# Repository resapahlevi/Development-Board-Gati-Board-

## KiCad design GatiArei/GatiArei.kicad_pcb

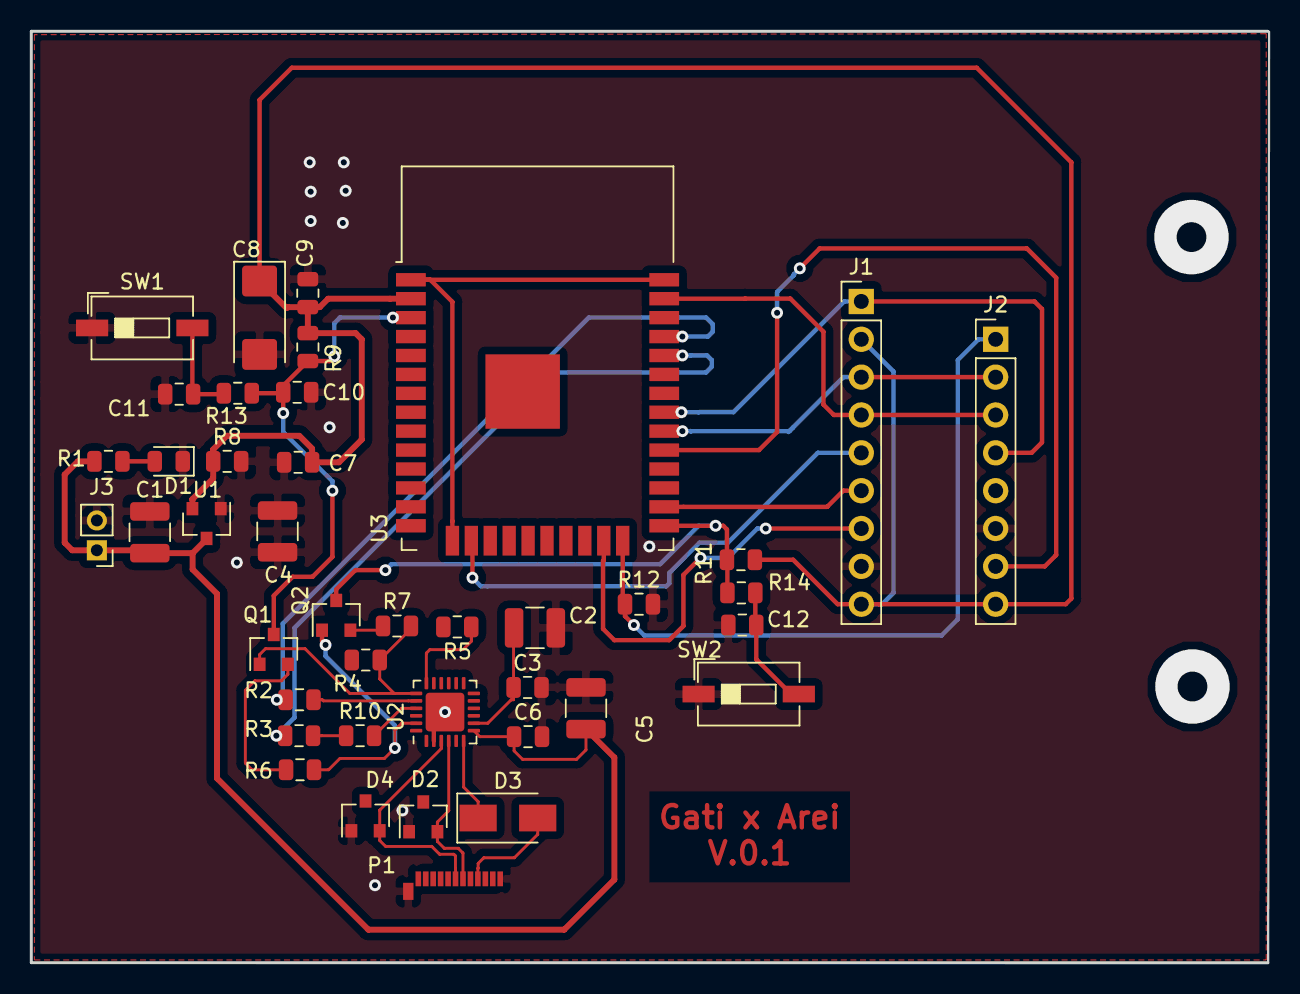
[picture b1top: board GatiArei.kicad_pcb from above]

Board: 2 copper layers, 83.1 x 62.5 mm, 41 parts (0 on the bottom side), 30 nets.

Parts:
C1, C2, C4, C5: 10uf/25v; C_1210_3225Metric
C3, C6: 0.1uf/25v; C_0805_2012Metric
C7: 22uf/25v; C_0805_2012Metric
C8: 100uf/6.3V; CP_EIA-6032-15_Kemet-U
C9: 1uf/10V; C_0805_2012Metric
C10: 1NF/50V; C_0805_2012Metric
C11, C12: 1nf/50V; C_0805_2012Metric
D1: LED_R; LED_0805_2012Metric
D2, D4: ESD5V; SOT-23
D3: 1N5819; D_SMA
J1: LCD_PORT; PinHeader_1x09_P2.54mm_Vertical
J2: RFID_PORT; PinHeader_1x08_P2.54mm_Vertical
J3: Bat_Con; PinHeader_1x02_P2.00mm_Vertical
P1: USB_C; USB_C_Plug_Molex_105444
Q1, Q2: S8050; SOT-23
R1: 2k; R_0805_2012Metric
R2, R3, R4, R5: 0R; R_0805_2012Metric
R6, R7, R9: 12K; R_0805_2012Metric
R8: 3.3k; R_0805_2012Metric
R10, R13, R14: 470R; R_0805_2012Metric
R11, R12: 5K; R_0805_2012Metric
SW1, SW2: SW1; SW_DIP_SPSTx01_Slide_6.7x4.1mm_W6.73mm_P2.54mm_LowProfile_J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
U1: MCP1700; SOT-23
U2: CP2102N; QFN-24-1EP_4x4mm_P0.5mm_EP2.6x2.6mm
U3: ESP32-WROOM-32

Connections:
CTS: R5.1, U2.18
DTR: Q2.1, R6.2, U2.23
EN: C10.1, Q1.3, R9.2, R13.1, U3.3
GND: C1.2, C2.2, C3.2, C4.1, C4.2, C5.2, C6.2, C7.2, C8.2, C9.2, C10.2, C11.2, C12.2, D1.1, D2.1, D4.1, J1.8, J2.6, J3.2, P1.A1, P1.A12, P1.B1, P1.B12, P1.S1, R8.2, R12.2, SW1.1, SW2.1, U1.1, U2.2, U2.25
IO0: Q2.3, R11.2, R14.1, U3.25
LCD_DC: J1.5, U3.16
LCD_RST: J1.6, U3.26
LCD_SS: J1.7, U3.23
unnamed: C11.1, R13.2, SW1.2
unnamed: C12.1, R14.2, SW2.2
unnamed: D1.2, R1.2
unnamed: D3.2, P1.A4, P1.A9, P1.B4, P1.B9
unnamed: Q1.2, R6.1
unnamed: Q2.2, R7.1
unnamed: R10.2, U2.21
unnamed: U3.1, U3.15, U3.38
RFID_RST: J2.7, U3.29
RFID_SS: J2.1, R12.1, U3.24
RTS: Q1.1, R4.1, R7.2, U2.19
RXD: R2.1, U2.20
RXD0: R3.2, U3.34
SPI_MISO: J1.1, J2.4, U3.31
SPI_MOSI: J1.4, J2.3, U3.37
SPI_SCK: J1.3, J2.2, U3.30
TXD: R3.1, R10.1
TXD0: R2.2, U3.35
USB_DN: D2.2, P1.A7, U2.4
USB_DP: D4.2, P1.A6, U2.3
VDD_ESP: C7.1, C8.1, C9.1, J1.2, J1.9, J2.8, R8.1, R9.1, R11.1, U1.2, U3.2
VDD_REGIN: C1.1, C2.1, C3.1, C5.1, C6.1, D3.1, J3.1, R1.1, U1.3, U2.6, U2.7, U2.8

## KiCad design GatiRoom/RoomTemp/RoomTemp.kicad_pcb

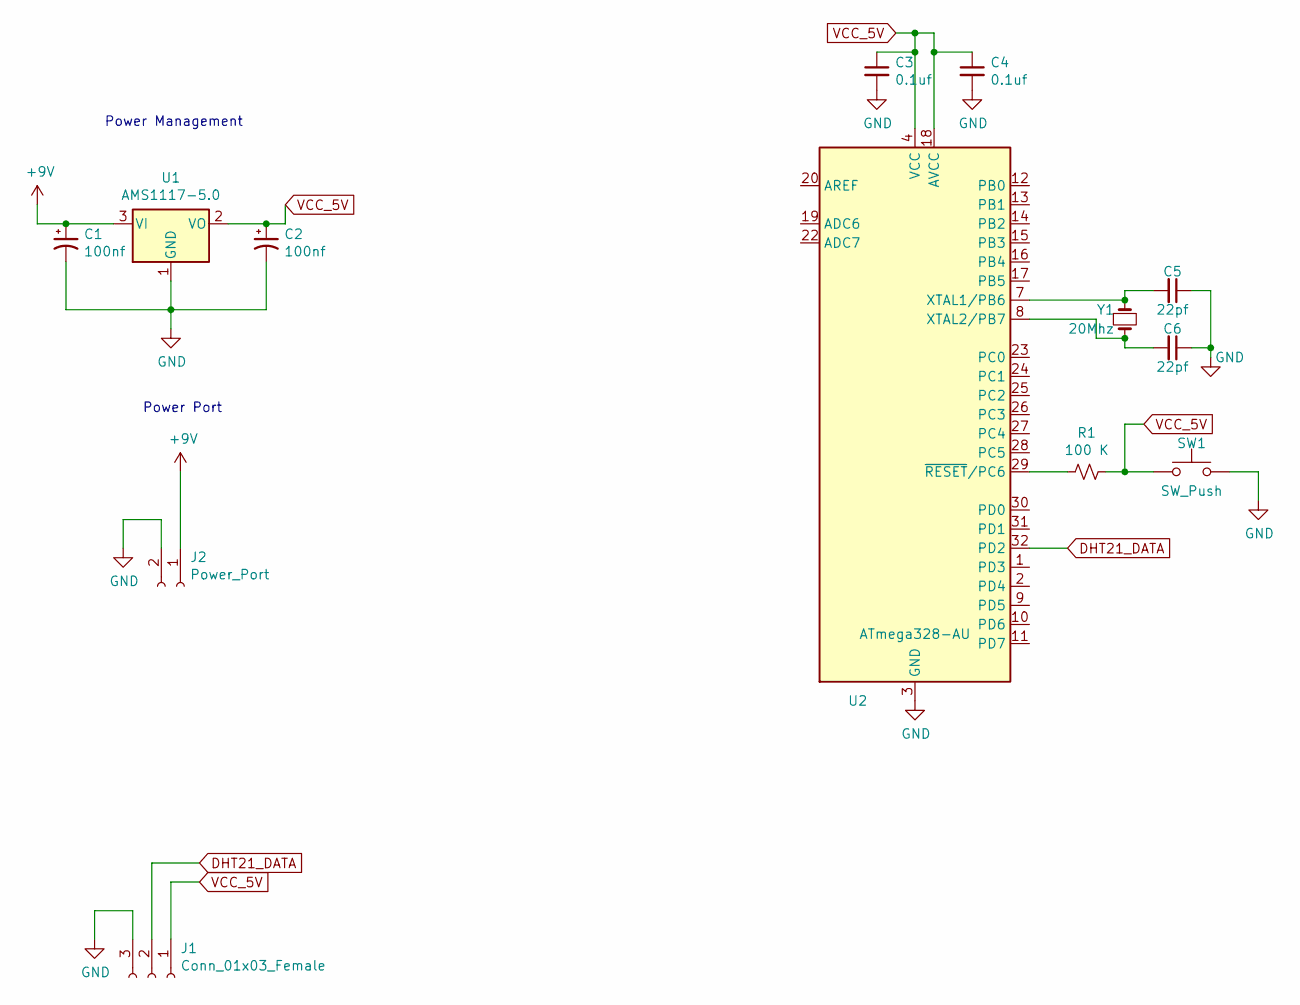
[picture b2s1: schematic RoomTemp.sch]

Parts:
C1, C2: 100nf; C_1206_3216Metric
C3, C4: 0.1uf; C_1206_3216Metric
C5, C6: 22pf; C_1206_3216Metric
J1: Conn_01x03_Female; PinHeader_1x03_P2.54mm_Horizontal
J2: Power_Port; PinHeader_1x02_P2.54mm_Horizontal
R1: 100 K; R_1206_3216Metric
SW1: SW_Push; SW_SPST_B3SL-1022P
U1: AMS1117-5.0; SOT-223-3_TabPin2
U2: ATmega328-AU; TQFP-32_7x7mm_P0.8mm
Y1: 20Mhz; Resonator-2Pin_W10.0mm_H5.0mm

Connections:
+9V: C1.1, J2.1, U1.3 (VI)
DHT21_DATA: J1.2, U2.32 (PD2)
GND: C1.2, C2.2, C3.2, C4.2, C5.1, C6.1, J1.3, J2.2, SW1.2, U1.1 (GND), U2.3 (GND), U2.5 (GND), U2.21 (GND)
unnamed: C5.2, U2.7 (XTAL1/PB6), Y1.1
unnamed: C6.2, U2.8 (XTAL2/PB7), Y1.2
unnamed: R1.2, U2.29 (~RESET~/PC6)
VCC_5V: C2.1, C3.1, C4.1, J1.1, R1.1, SW1.1, U1.2 (VO), U2.4 (VCC), U2.6 (VCC), U2.18 (AVCC)

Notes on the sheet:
Power Management
Power Port

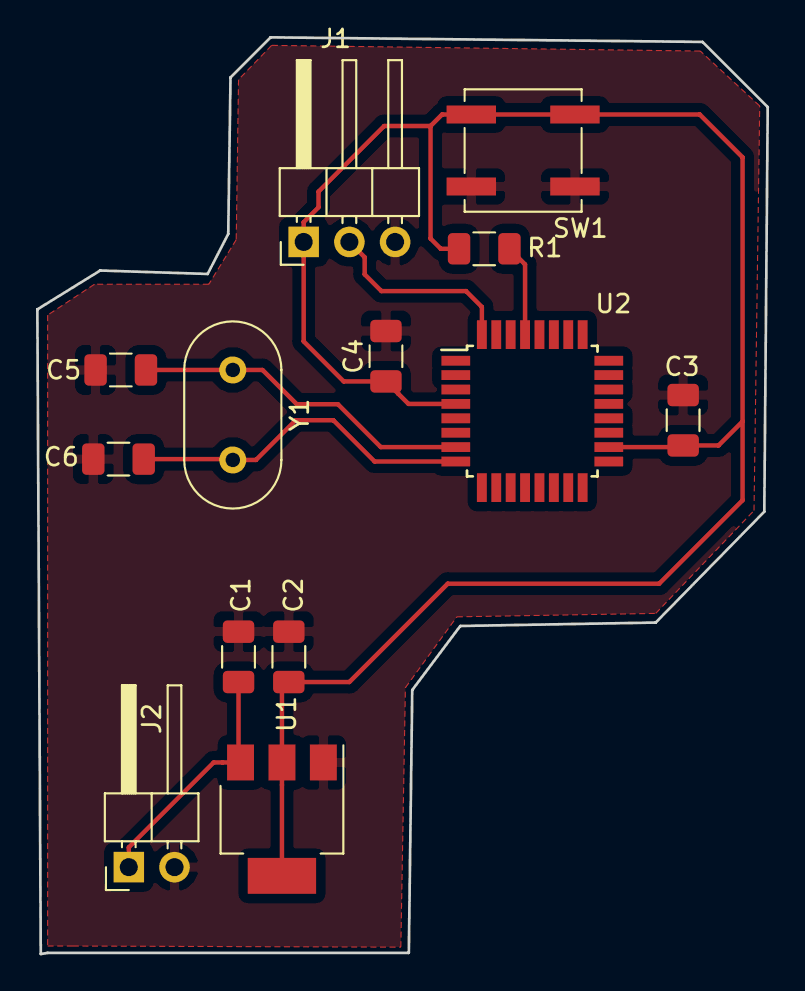
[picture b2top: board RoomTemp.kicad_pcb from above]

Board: 2 copper layers, 40.6 x 50.9 mm, 13 parts (0 on the bottom side), 7 nets.

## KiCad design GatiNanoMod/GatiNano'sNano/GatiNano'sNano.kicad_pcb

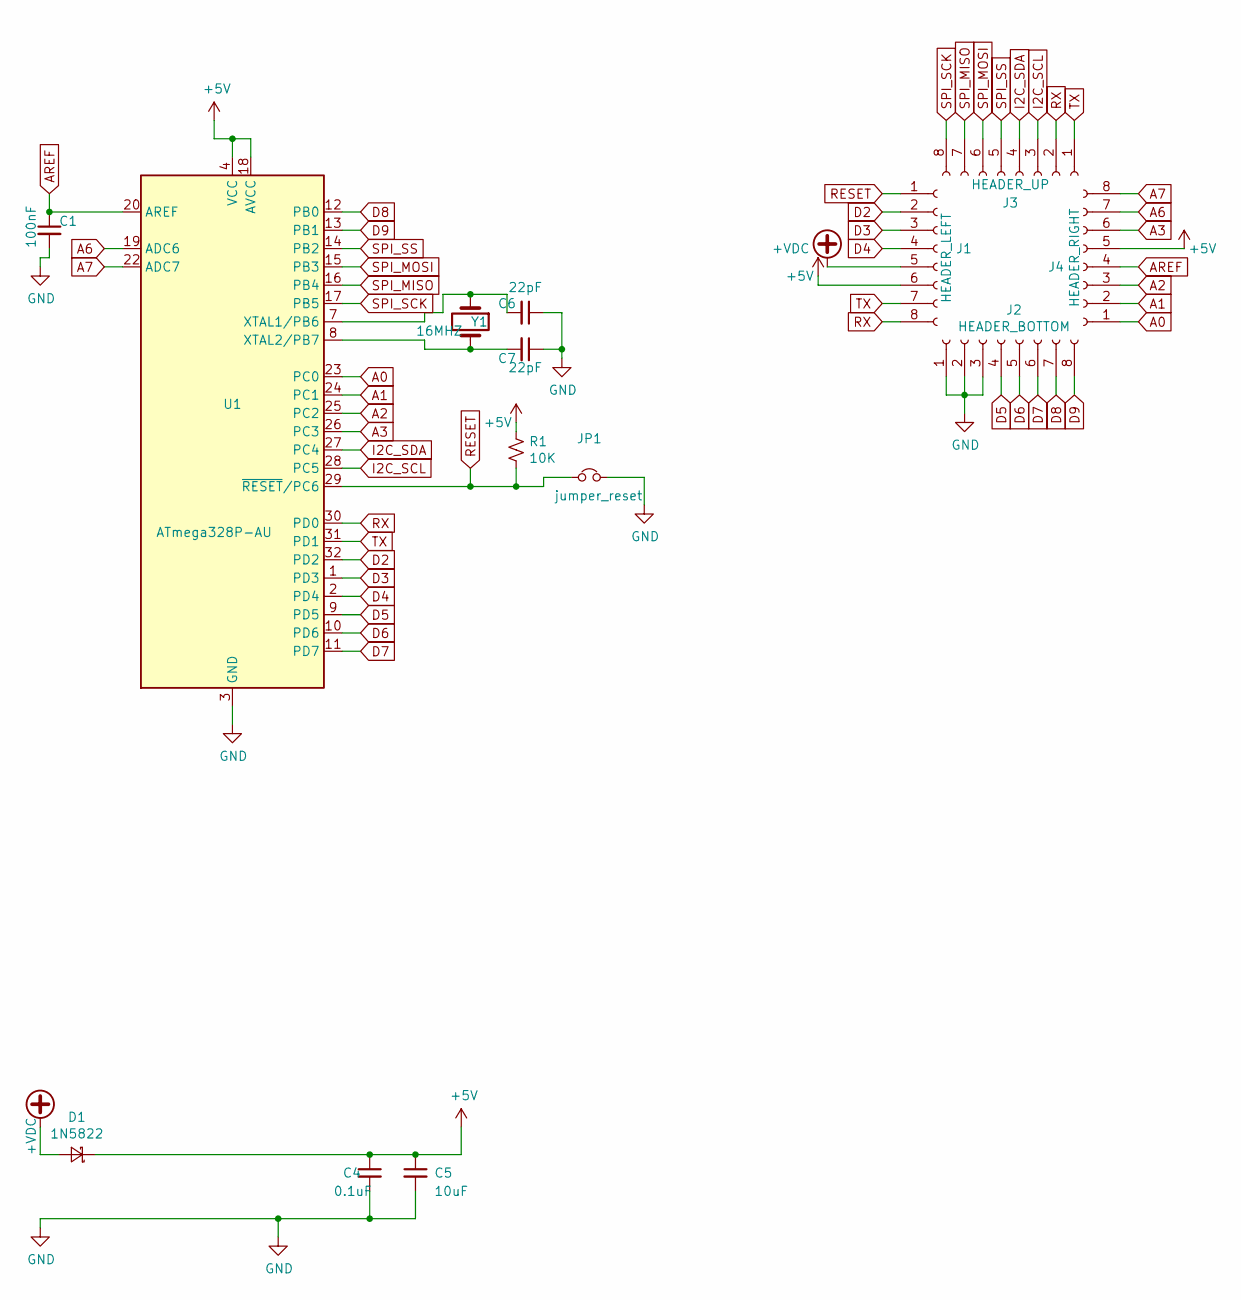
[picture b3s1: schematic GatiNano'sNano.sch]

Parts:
C1: 100nF; C_0603_1608Metric
C4: 0.1uF; C_0603_1608Metric
C5: 10uF; C_0603_1608Metric
C6, C7: 22pF; C_0603_1608Metric
D1: 1N5822; D_0603_1608Metric
J1: HEADER_LEFT; PinHeader_1x08_P2.00mm_Vertical
J2: HEADER_BOTTOM; PinHeader_1x08_P2.00mm_Vertical
J3: HEADER_UP; PinHeader_1x08_P2.00mm_Vertical
J4: HEADER_RIGHT; PinHeader_1x08_P2.00mm_Vertical
JP1: jumper_reset; SolderJumper-2_P1.3mm_Open_RoundedPad1.0x1.5mm
R1: 10K; R_0603_1608Metric
U1: ATmega328P-AU; TQFP-32_7x7mm_P0.8mm
Y1: 16MHZ; Crystal_SMD_2012-2Pin_2.0x1.2mm

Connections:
+5V: C4.1, C5.1, D1.1 (K), J1.6, J4.5, R1.1, U1.4 (VCC), U1.6 (VCC), U1.18 (AVCC)
+VDC: D1.2 (A), J1.5
A0: J4.1, U1.23 (PC0)
A1: J4.2, U1.24 (PC1)
A2: J4.3, U1.25 (PC2)
A3: J4.6, U1.26 (PC3)
A6: J4.7, U1.19 (ADC6)
A7: J4.8, U1.22 (ADC7)
AREF: C1.1, J4.4, U1.20 (AREF)
D2: J1.2, U1.32 (PD2)
D3: J1.3, U1.1 (PD3)
D4: J1.4, U1.2 (PD4)
D5: J2.4, U1.9 (PD5)
D6: J2.5, U1.10 (PD6)
D7: J2.6, U1.11 (PD7)
D8: J2.7, U1.12 (PB0)
D9: J2.8, U1.13 (PB1)
GND: C1.2, C4.2, C5.2, C6.1, C7.1, J2.1, J2.2, J2.3, JP1.2, U1.3 (GND), U1.5 (GND), U1.21 (GND)
I2C_SCL: J3.3, U1.28 (PC5)
I2C_SDA: J3.4, U1.27 (PC4)
unnamed: C6.2, U1.7 (XTAL1/PB6), Y1.1
unnamed: C7.2, U1.8 (XTAL2/PB7), Y1.2
RESET: J1.1, JP1.1, R1.2, U1.29 (~RESET~/PC6)
RX: J1.8, J3.2, U1.30 (PD0)
SPI_MISO: J3.7, U1.16 (PB4)
SPI_MOSI: J3.6, U1.15 (PB3)
SPI_SCK: J3.8, U1.17 (PB5)
SPI_SS: J3.5, U1.14 (PB2)
TX: J1.7, J3.1, U1.31 (PD1)

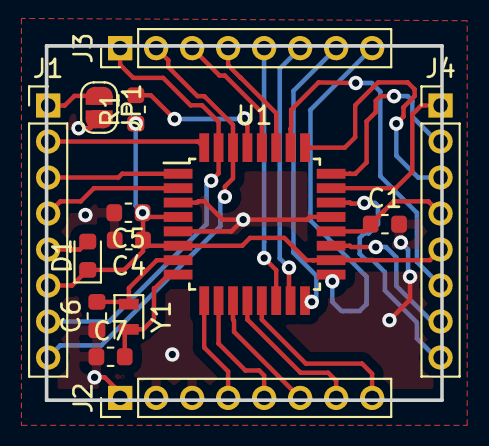
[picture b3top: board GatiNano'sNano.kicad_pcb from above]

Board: 2 copper layers, 22.0 x 19.7 mm, 14 parts (0 on the bottom side), 29 nets.

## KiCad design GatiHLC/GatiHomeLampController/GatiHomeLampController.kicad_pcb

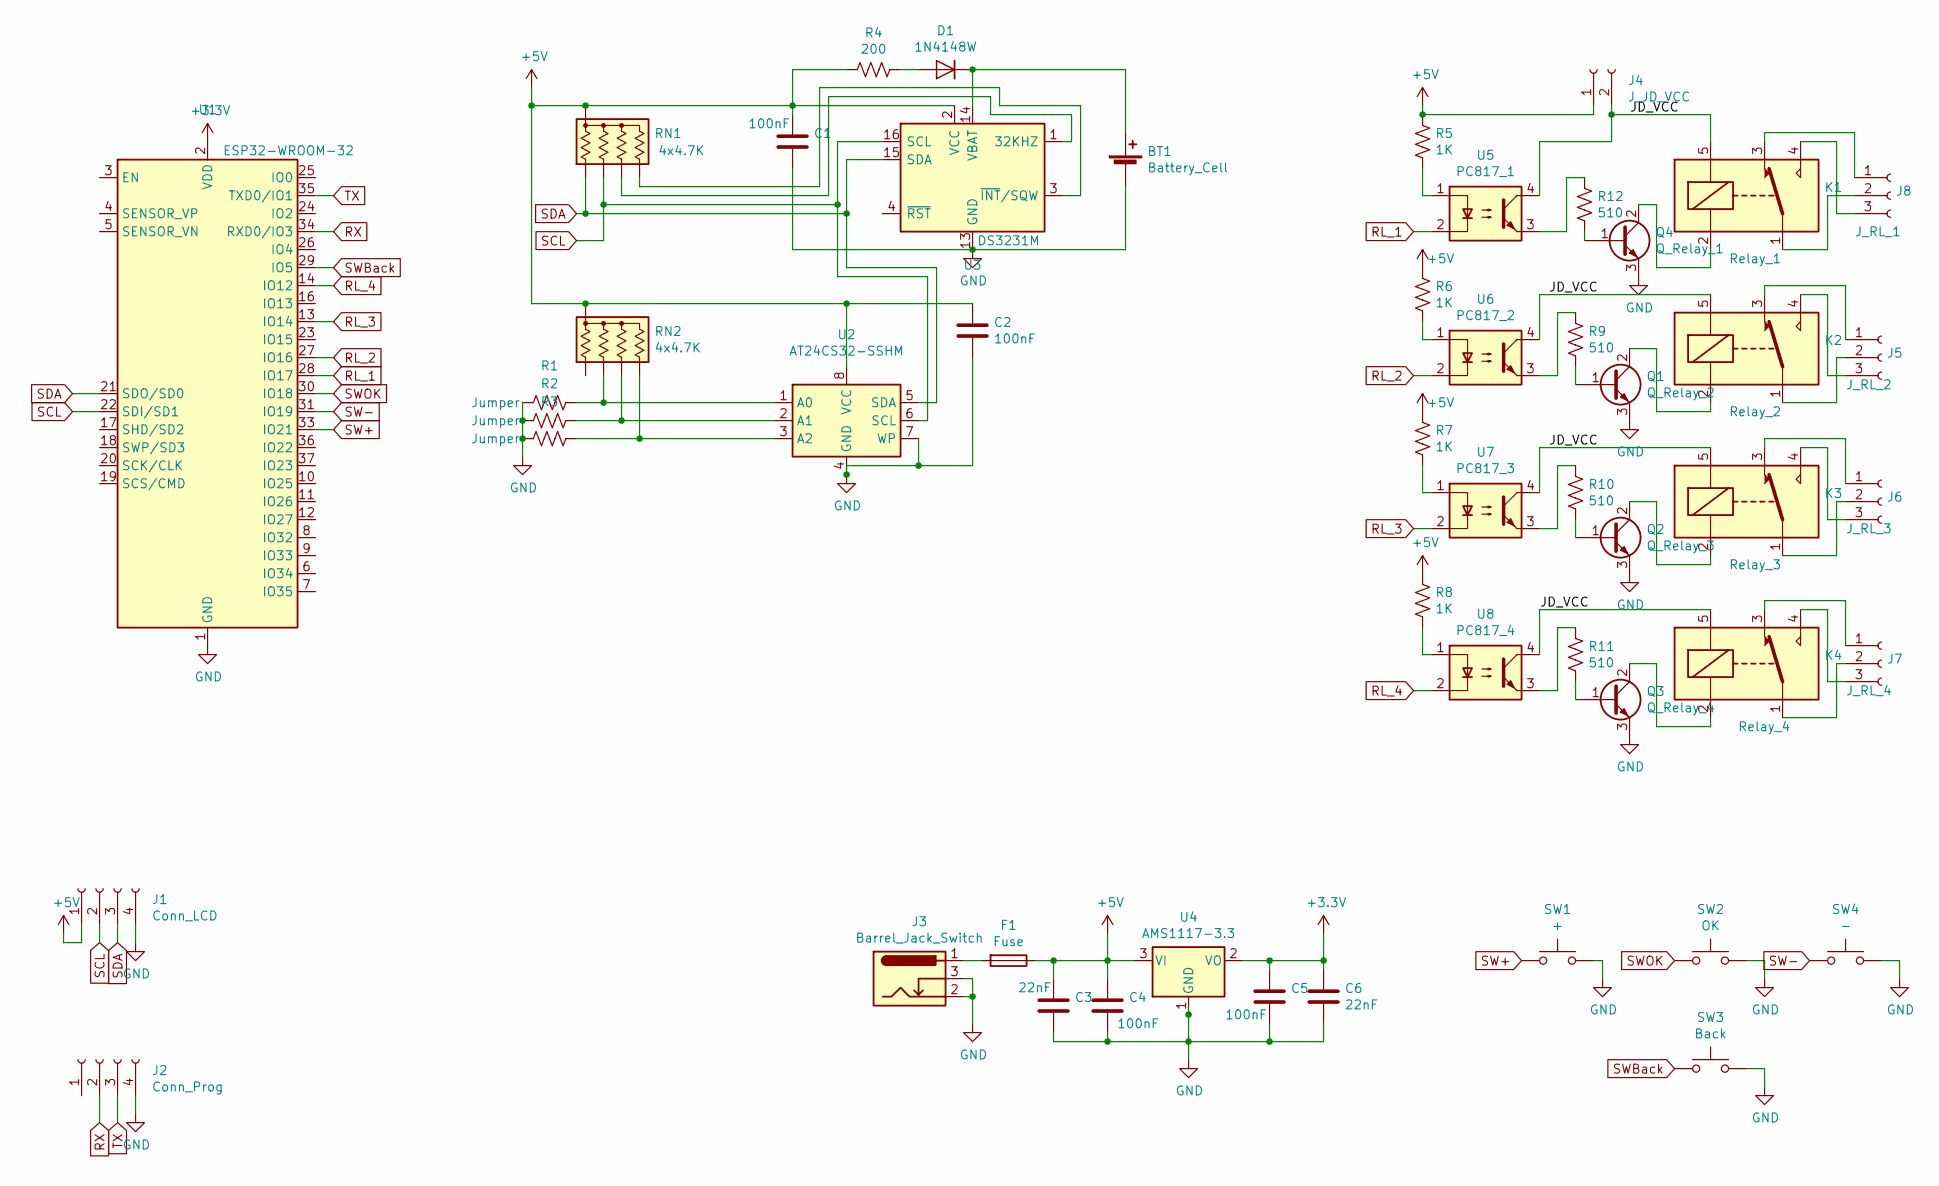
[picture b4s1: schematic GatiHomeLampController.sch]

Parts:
BT1: Battery_Cell; BatteryHolder_MPD_BC2003_1x2032
C1, C2, C4, C5: 100nF; C_1206_3216Metric_Pad1.42x1.75mm_HandSolder
C3, C6: 22nF; C_1206_3216Metric_Pad1.42x1.75mm_HandSolder
D1: 1N4148W; D_SOD-123
F1: Fuse; Fuse_1206_3216Metric
J1: Conn_LCD; PinHeader_1x04_P2.54mm_Vertical
J2: Conn_Prog; PinHeader_1x04_P2.54mm_Vertical
J3: Barrel_Jack_Switch; BarrelJack_CUI_PJ-102AH_Horizontal
J4: J_JD_VCC; PinHeader_1x02_P2.54mm_Vertical
J5: J_RL_2; TerminalBlock_Altech_AK300-3_P5.00mm
J6: J_RL_3; TerminalBlock_Altech_AK300-3_P5.00mm
J7: J_RL_4; TerminalBlock_Altech_AK300-3_P5.00mm
J8: J_RL_1; TerminalBlock_Altech_AK300-3_P5.00mm
K1: Relay_1; Relay_SPDT_SANYOU_SRD_Series_Form_C
K2: Relay_2; Relay_SPDT_SANYOU_SRD_Series_Form_C
K3: Relay_3; Relay_SPDT_SANYOU_SRD_Series_Form_C
K4: Relay_4; Relay_SPDT_SANYOU_SRD_Series_Form_C
Q1: Q_Relay_2; SOT-23
Q2: Q_Relay_3; SOT-23
Q3: Q_Relay_4; SOT-23
Q4: Q_Relay_1; SOT-23
R1, R2, R3: Jumper; R_1206_3216Metric
R4: 200; R_1206_3216Metric
R5, R6, R7, R8: 1K; R_1206_3216Metric
R9, R10, R11, R12: 510; R_1206_3216Metric
RN1, RN2: 4x4.7K; R_Array_Convex_4x1206
SW1: +; SW_PUSH-12mm
SW2: OK; SW_PUSH-12mm
SW3: Back; SW_PUSH-12mm
SW4: -; SW_PUSH-12mm
U1: ESP32-WROOM-32
U2: AT24CS32-SSHM; SOIC-8_3.9x4.9mm_P1.27mm
U3: DS3231M; SOIC-16W_7.5x10.3mm_P1.27mm
U4: AMS1117-3.3; SOT-223-3_TabPin2
U5: PC817_1; DIP-4_W7.62mm
U6: PC817_2; DIP-4_W7.62mm
U7: PC817_3; DIP-4_W7.62mm
U8: PC817_4; DIP-4_W7.62mm

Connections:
+3V3: C5.1, C6.1, U1.2 (VDD), U4.2 (VO)
+5V: C1.1, C2.1, C3.1, C4.1, F1.1, J1.1, J4.1, R4.2, R5.1, R6.1, R7.1, R8.1, RN1.1 (common), RN2.1 (common), U2.8 (VCC), U3.2 (VCC), U4.3 (VI)
/JD_VCC: J4.2, K1.5, K2.5, K3.5, K4.5, U5.4, U6.4, U7.4, U8.4
GND: BT1.2 (-), C1.2, C2.2, C3.2, C4.2, C5.2, C6.2, J1.4, J2.4, J3.2, J3.3, Q1.3 (E), Q2.3 (E), Q3.3 (E), Q4.3 (E), R1.2, R2.2, R3.2, SW1.2, SW2.2, SW3.2, SW4.2, U1.1 (GND), U1.15 (GND), U1.38 (GND), U2.4 (GND), U2.7 (WP), U3.5 (GND), U3.6 (GND), U3.7 (GND), U3.8 (GND), U3.9 (GND), U3.10 (GND), U3.11 (GND), U3.12 (GND), U3.13 (GND), U4.1 (GND)
unnamed: BT1.1 (+), D1.1 (K), U3.14 (VBAT)
unnamed: D1.2 (A), R4.1
unnamed: F1.2, J3.1
unnamed: J5.1, K2.3
unnamed: J5.2, K2.1
unnamed: J5.3, K2.4
unnamed: J6.1, K3.3
unnamed: J6.2, K3.1
unnamed: J6.3, K3.4
unnamed: J7.1, K4.3
unnamed: J7.2, K4.1
unnamed: J7.3, K4.4
unnamed: J8.1, K1.3
unnamed: J8.2, K1.1
unnamed: J8.3, K1.4
unnamed: K1.2, Q4.2 (C)
unnamed: K2.2, Q1.2 (C)
unnamed: K3.2, Q2.2 (C)
unnamed: K4.2, Q3.2 (C)
unnamed: Q1.1 (B), R9.1
unnamed: Q2.1 (B), R10.1
unnamed: Q3.1 (B), R11.1
unnamed: Q4.1 (B), R12.1
unnamed: R1.1, RN2.3 (R2), U2.1 (A0)
unnamed: R2.1, RN2.4 (R3), U2.2 (A1)
unnamed: R3.1, RN2.5 (R4), U2.3 (A2)
unnamed: R5.2, U5.1
unnamed: R6.2, U6.1
unnamed: R7.2, U7.1
unnamed: R8.2, U8.1
unnamed: R9.2, U6.3
unnamed: R10.2, U7.3
unnamed: R11.2, U8.3
unnamed: R12.2, U5.3
unnamed: RN1.4 (R3), U3.1 (32KHZ)
unnamed: RN1.5 (R4), U3.3 (~INT~/SQW)
RL_1: U1.28 (IO17), U5.2
RL_2: U1.27 (IO16), U6.2
RL_3: U1.13 (IO14), U7.2
RL_4: U1.14 (IO12), U8.2
RX: J2.2, U1.34 (RXD0/IO3)
SCL: J1.2, RN1.3 (R2), U1.22 (SDI/SD1), U2.6 (SCL), U3.16 (SCL)
SDA: J1.3, RN1.2 (R1), U1.21 (SDO/SD0), U2.5 (SDA), U3.15 (SDA)
SW+: SW1.1, U1.33 (IO21)
SW-: SW4.1, U1.31 (IO19)
SWBack: SW3.1, U1.29 (IO5)
SWOK: SW2.1, U1.30 (IO18)
TX: J2.3, U1.35 (TXD0/IO1)

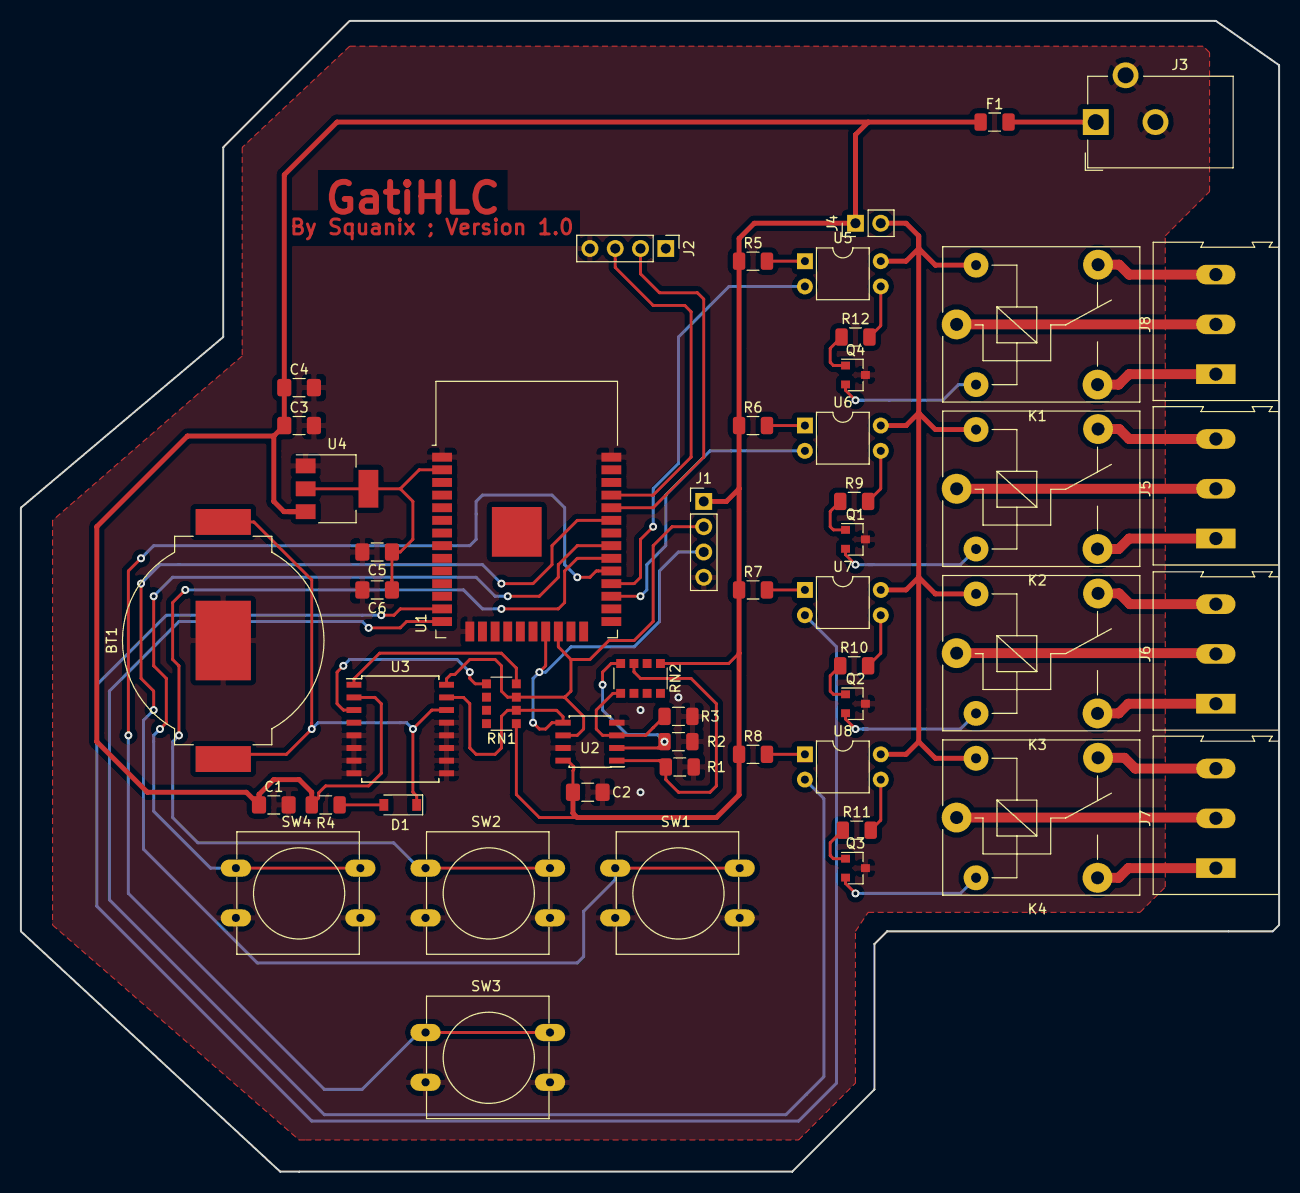
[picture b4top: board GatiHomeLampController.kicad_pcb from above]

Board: 2 copper layers, 126.4 x 115.6 mm, 51 parts (0 on the bottom side), 52 nets.

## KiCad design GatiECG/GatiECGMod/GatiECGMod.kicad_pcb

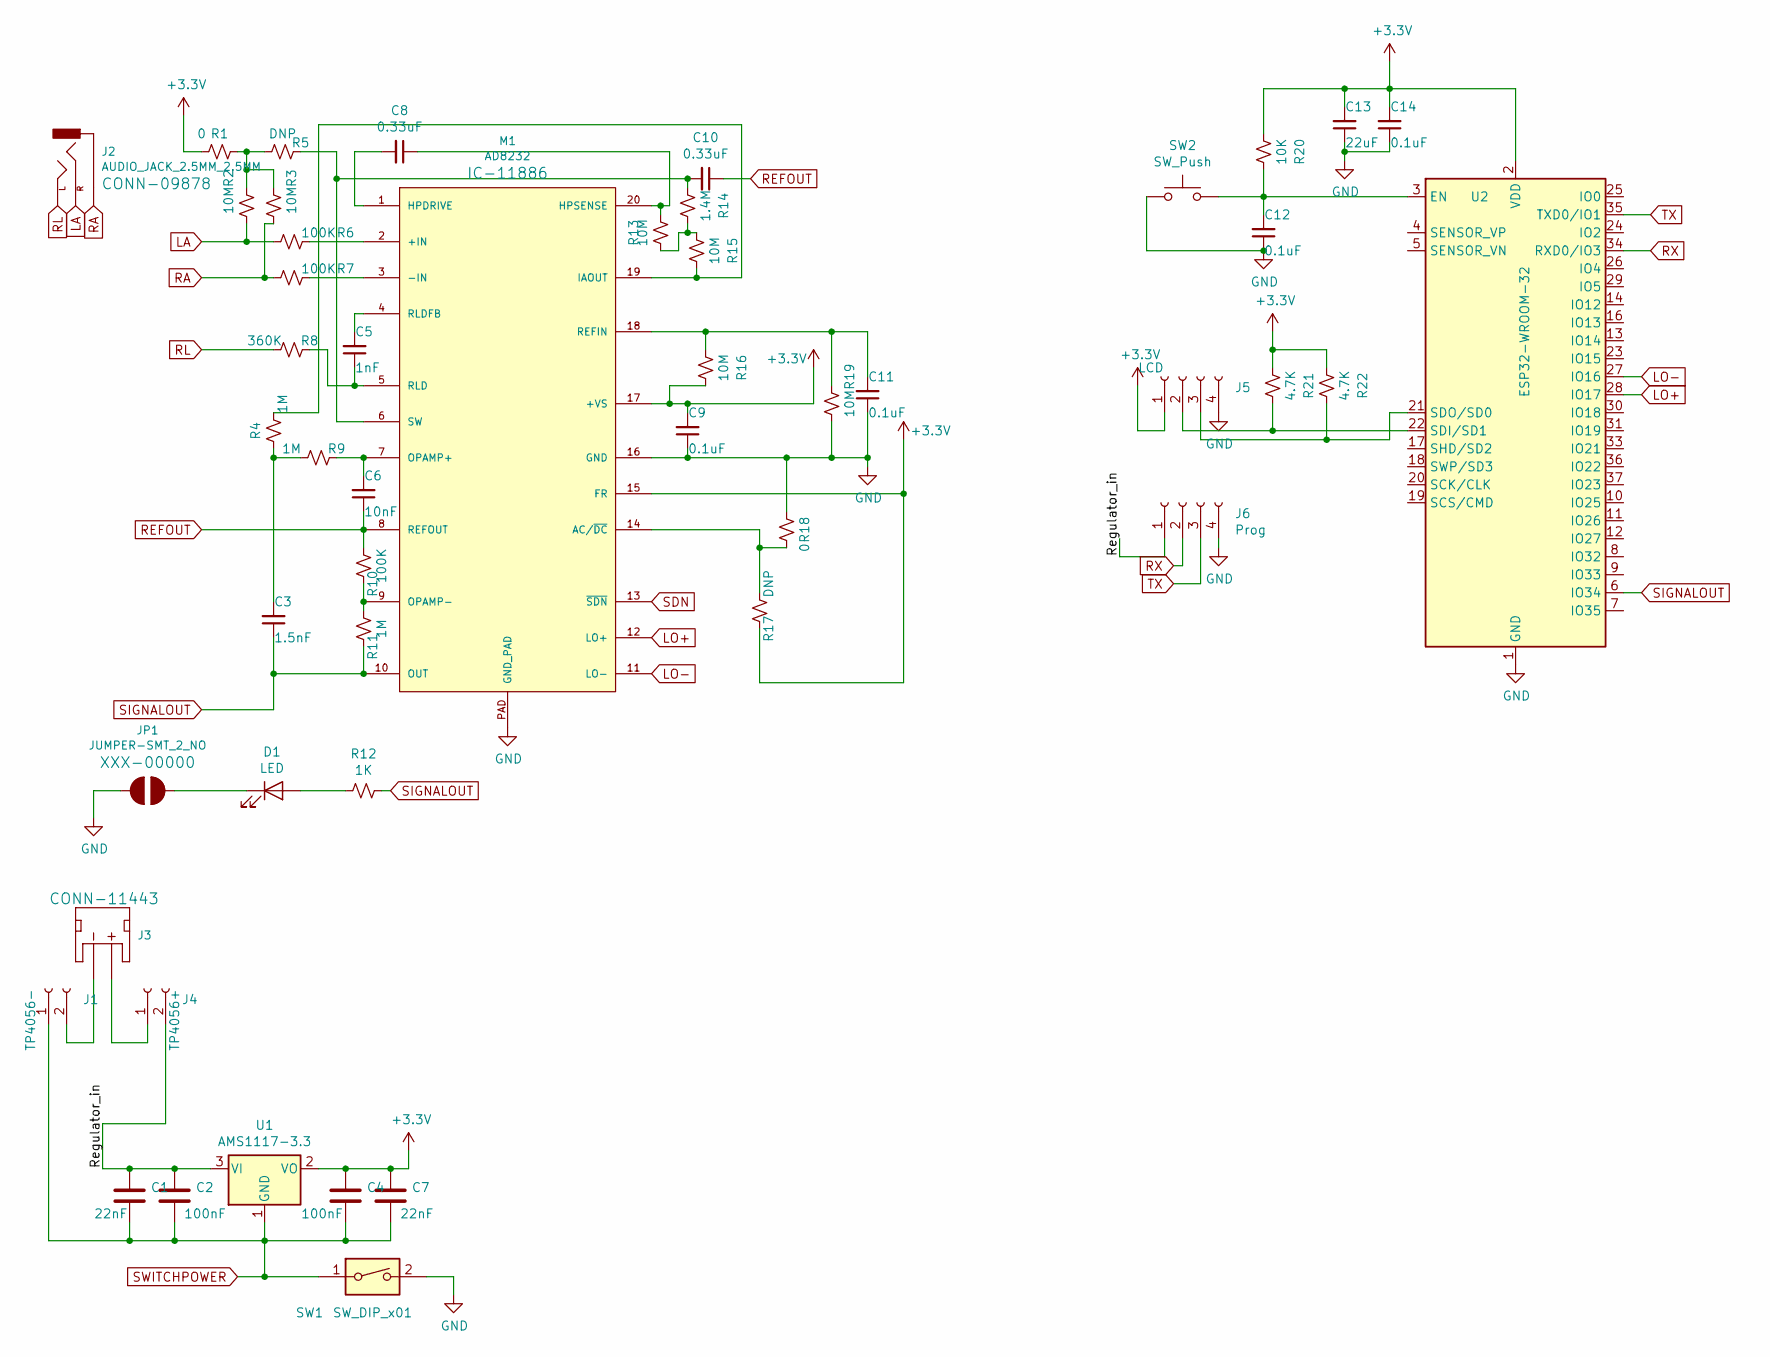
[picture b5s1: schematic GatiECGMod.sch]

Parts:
C1, C7: 22nF; C_1206_3216Metric
C2, C4: 100nF; C_1206_3216Metric
C3: 1.5nF; C_1206_3216Metric
C5: 1nF; C_1206_3216Metric
C6: 10nF; C_1206_3216Metric
C8, C10: 0.33uF; C_1206_3216Metric
C9, C11, C12, C14: 0.1uF; C_1206_3216Metric
C13: 22uF; C_1206_3216Metric
D1: LED; D_1206_3216Metric
J1: TP4056-; PinSocket_1x02_P2.54mm_Vertical
J2: AUDIO_JACK_2.5MM_2.5MM; AUDIO-JACK-3.5MM-SMD
J3: LIPO_Port; JST_PH_B2B-PH-K_1x02_P2.00mm_Vertical
J4: TP4056+; PinSocket_1x02_P2.54mm_Vertical
J5: LCD; PinHeader_1x04_P2.54mm_Vertical
J6: Prog; PinHeader_1x04_P2.54mm_Vertical
JP1: JUMPER-SMT_2_NO; SolderJumper-2_P1.3mm_Open_Pad1.0x1.5mm
M1: AD8232; LFCSP_20
R1, R18: 0; R_1206_3216Metric
R2, R3, R13, R15, R16, R19: 10M; R_1206_3216Metric
R4, R9, R11: 1M; R_1206_3216Metric
R5, R17: DNP; R_1206_3216Metric
R6, R7, R10: 100K; R_1206_3216Metric
R8: 360K; R_1206_3216Metric
R12: 1K; R_1206_3216Metric
R14: 1.4M; R_1206_3216Metric
R20: 10K; R_1206_3216Metric
R21, R22: 4.7K; R_1206_3216Metric
SW1: SW_DIP_x01; SW_DIP_SPSTx01_Slide_9.78x4.72mm_W7.62mm_P2.54mm
SW2: SW_Push; SW_DIP_SPSTx01_Slide_6.7x4.1mm_W6.73mm_P2.54mm_LowProfile_J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
U1: AMS1117-3.3; SOT-223-3_TabPin2
U2: ESP32-WROOM-32

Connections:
+3V3: C4.1, C7.1, C9.2, C13.2, C14.2, J5.1, M1.15 (FR), M1.17 (+VS), R1.2, R16.1, R17.1, R20.2, R21.2, R22.2, U1.2 (VO), U2.2 (VDD)
/Regulator_in: C1.1, C2.1, J4.2, J6.1, U1.3 (VI)
GND: C9.1, C11.1, C12.1, C13.1, C14.1, J5.4, J6.4, JP1.1, M1.16 (GND), M1.PAD (GND_PAD), R18.2, R19.1, SW1.2, SW2.1, U2.1 (GND), U2.15 (GND), U2.38 (GND)
LA: J2.TIP (RIGHT), R2.2, R6.2
LO+: M1.12 (LO+), U2.28 (IO17)
LO-: M1.11 (LO-), U2.27 (IO16)
unnamed: C3.2, R4.1, R9.2
unnamed: C5.1, M1.5 (RLD), R8.1
unnamed: C5.2, M1.4 (RLDFB)
unnamed: C6.2, M1.7 (OPAMP+), R9.1
unnamed: C8.1, M1.20 (HPSENSE), R13.2
unnamed: C8.2, M1.1 (HPDRIVE)
unnamed: C10.2, M1.6 (SW), R5.1, R14.2
unnamed: C11.2, M1.18 (REFIN), R16.2, R19.2
unnamed: C12.2, R20.1, SW2.2, U2.3 (EN)
unnamed: D1.1 (K), JP1.2
unnamed: D1.2 (A), R12.2
unnamed: J1.2, J3.1 (-)
unnamed: J3.2 (+), J4.1
unnamed: J5.2, R21.1, U2.22 (SDI/SD1)
unnamed: J5.3, R22.1, U2.21 (SDO/SD0)
unnamed: M1.2 (+IN), R6.1
unnamed: M1.3 (-IN), R7.1
unnamed: M1.9 (OPAMP-), R10.1, R11.2
unnamed: M1.14 (AC/~DC), R17.2, R18.1
unnamed: M1.19 (IAOUT), R4.2, R15.1
unnamed: R1.1, R2.1, R3.1, R5.2
unnamed: R13.1, R14.1, R15.2
RA: J2.RING (SLEEVE), R3.2, R7.2
REFOUT: C6.1, C10.1, M1.8 (REFOUT), R10.2
RL: J2.SHIE (LEFT), R8.2
RX: J6.2, U2.34 (RXD0/IO3)
SDN: M1.13 (~SDN)
SIGNALOUT: C3.1, M1.10 (OUT), R11.1, R12.1, U2.6 (IO34)
SWITCHPOWER: C1.2, C2.2, C4.2, C7.2, J1.1, SW1.1, U1.1 (GND)
TX: J6.3, U2.35 (TXD0/IO1)

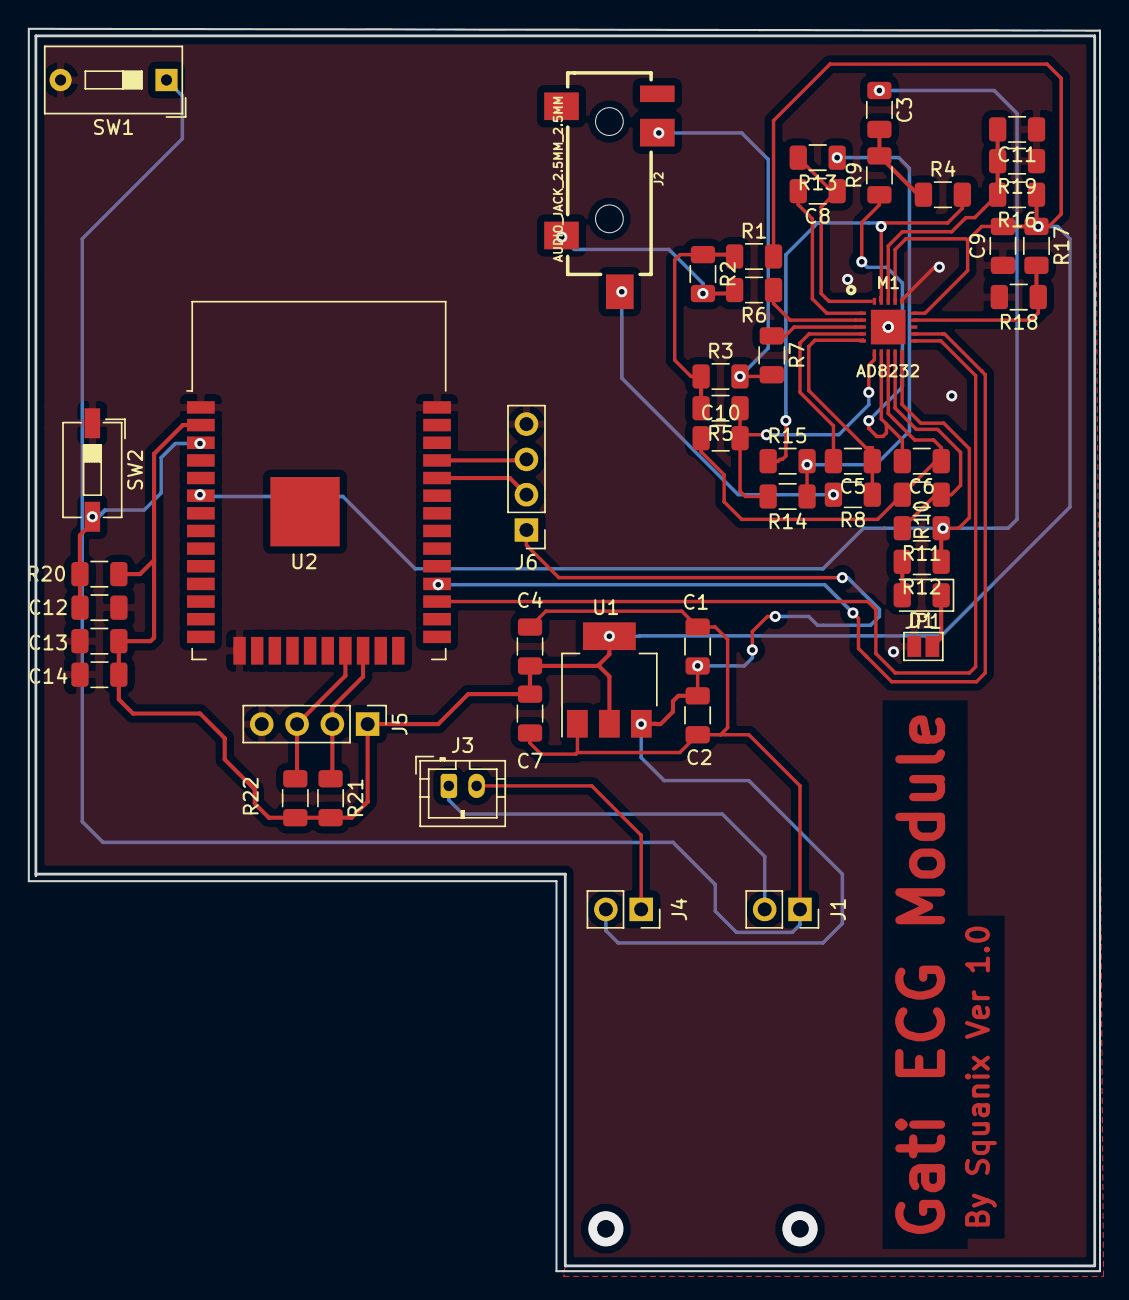
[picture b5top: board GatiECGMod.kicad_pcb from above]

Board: 2 copper layers, 77.0 x 89.4 mm, 49 parts (0 on the bottom side), 34 nets.

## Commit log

2021-02-05 Init
2021-02-06 Init for Areimember Board
2021-02-06 ESP32 manual schematic
2021-02-07 Adding the RFID and LCD port
2021-02-09 Adding Display Port
2021-02-09 Generate PCB design
2021-02-09 support fix
2021-02-14 Raspberry pi zero retro game
2021-02-19 Adding PCB design
